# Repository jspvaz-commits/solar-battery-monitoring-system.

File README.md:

# solar-battery-monitoring-system.
Overview 
A KiCad electronic design project for a proposed solar-powered lithium-ion battery monitoring system. 

Objectives 
- Design the circuit schematic. 
- Convert the schematic into a PCB layout. 
- Explore the integration of battery charging, voltage/current monitoring and display functions. 

Components 
- ESP32 
- TP4056 charging module 
- INA219 voltage/current sensor 
- OLED display 
- 18650 lithium-ion battery
- Solar panel 

Design Tools 
KiCad — schematic capture and PCB layout. 

Design Files 
- “schematic/” — schematic PDF and native KiCad file. 
- “pcb/” — PCB layout and native KiCad file. 
- “images/” — screenshots of the schematic and PCB. 

Project Status 
Schematic and PCB design stage. Physical fabrication and hardware testing have not yet been completed. 

Future Work 
- Review the schematic and PCB design. 
- Verify electrical connections and design rules. 
- Fabricate the PCB and test the system when hardware access is available.

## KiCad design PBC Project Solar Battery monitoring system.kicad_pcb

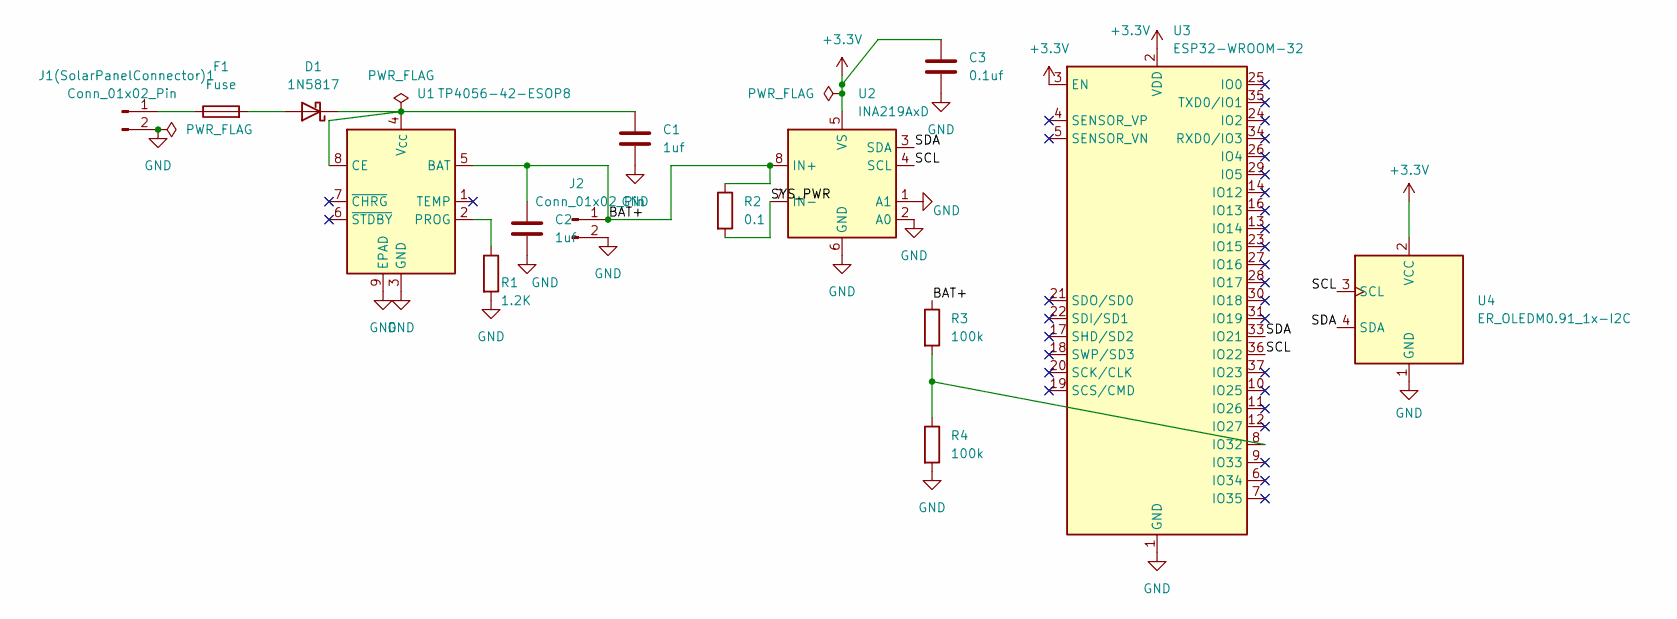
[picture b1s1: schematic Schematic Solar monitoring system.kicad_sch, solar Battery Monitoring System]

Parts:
C1, C2: 1uf; C_0805_2012Metric
C3: 0.1uf; C_0805_2012Metric
D1: 1N5817; D_DO-41_SOD81_P10.16mm_Horizontal
F1: Fuse; Fuse_1206_3216Metric
J1(SolarPanelConnector)1, J2: Conn_01x02_Pin; PinHeader_1x02_P2.54mm_Vertical
R1: 1.2K; R_0805_2012Metric
R2: 0.1; R_0805_2012Metric
R3, R4: 100k; R_0805_2012Metric
U1: TP4056-42-ESOP8; SOIC-8-1EP_3.9x4.9mm_P1.27mm_EP2.41x3.3mm_ThermalVias
U2: INA219AxD; SOIC-8_3.9x4.9mm_P1.27mm
U3: ESP32-WROOM-32
U4: ER_OLEDM0.91_1x-I2C

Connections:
+3.3V: C3.1, U2.5 (VS), U3.2 (VDD), U3.3 (EN), U4.2 (VCC)
/BAT+: C2.1, J2.1, R2.1, R3.1, U1.5 (BAT), U2.8 (IN+)
/SCL: U2.4 (SCL), U3.36 (IO22), U4.3 (SCL)
/SDA: U2.3 (SDA), U3.33 (IO21), U4.4 (SDA)
/SYS_PWR: R2.2, U2.7 (IN-)
GND: C1.2, C2.2, C3.2, J1(SolarPanelConnector)1.2, J2.2, R1.2, R4.2, U1.3 (GND), U1.9 (EPAD), U2.1 (A1), U2.2 (A0), U2.6 (GND), U3.1 (GND), U3.15 (GND), U3.38 (GND), U3.39 (GND), U4.1 (GND)
unnamed: D1.2 (A), F1.2
unnamed: C1.1, D1.1 (K), U1.4 (V_{CC}), U1.8 (CE)
unnamed: F1.1, J1(SolarPanelConnector)1.1
unnamed: R1.1, U1.2 (PROG)
unnamed: R3.2, R4.1, U3.8 (IO32)

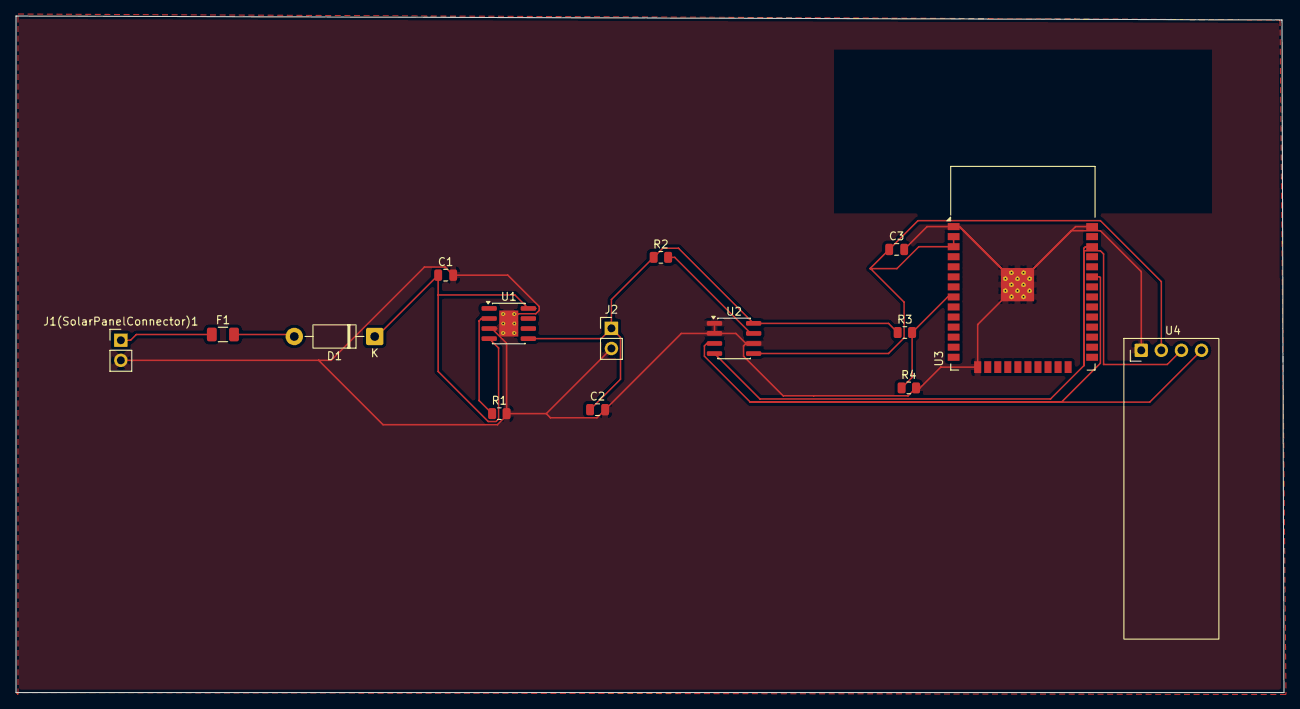
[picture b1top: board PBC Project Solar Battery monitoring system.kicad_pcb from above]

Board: 2 copper layers, 160.2 x 85.5 mm, 15 parts (0 on the bottom side), 11 nets.
